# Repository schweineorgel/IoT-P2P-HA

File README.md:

Demostraciones reales del sistema disponibles en video (ver sección “Demostraciones en video”).

# Sistema IoT descentralizado con ESP32 y ESP-NOW

Sistema de automatización doméstica diseñado para operar de forma autónoma,
segura y tolerante a fallos, utilizando comunicación peer-to-peer entre nodos
ESP32 mediante ESP-NOW, sin dependencia de red Wi-Fi ni broker central.

## Alcance del repositorio y estructura de diseño

Este repositorio documenta el proceso completo de diseño, prototipado, validación experimental e iteración de un sistema IoT descentralizado con ESP32 y ESP-NOW.

Los módulos incluidos pueden encontrarse en distintos estados de abstracción:
- Versiones finales con esquemáticos y diseños PCB.
- Placas de interconexión (solo PCB) orientadas a exponer pines físicos.
- Versiones preliminares o simplificadas utilizadas durante el proceso de
  validación experimental.

Cada módulo se documenta en su propio directorio dentro de `hardware/`,
incluyendo:
- El propósito funcional.
- Nivel de abstracción (esquemático completo, solo PCB, placa de interconexión).
- Relación entre diseño y la implementación física real.
- Decisiones de diseño relevantes y limitaciones conocidas.

La estructura general del directorio `hardware/` es la siguiente:

```
hardware/
├── nodemcu_sensor_pcb
├── nodemcu_ssr_pcb
├── sensor_pcb
└── ssr_pcb
```
Cada uno de estos directorios incluye su propio README detallado.

## Cómo leer este repositorio

Este repositorio no está orientado a la reproducción directa del sistema,
sino a la comprensión del proceso de diseño y validación.

Se recomienda el siguiente orden de lectura:

1. README principal (este archivo), para entender la arquitectura general.
2. Directorio `hardware/`, donde cada módulo cuenta con un README específico.
3. Directorios de firmware y configuración (ESPHome / Home Assistant), según interés.

Cada módulo de hardware debe interpretarse como una unidad independiente,
con su propio contexto, alcance y nivel de madurez.

## Arquitectura general

El sistema está compuesto por nodos ESP32 que toman decisiones localmente y
se comunican entre sí mediante ESP-NOW. La supervisión mediante Home Assistant
es opcional y no afecta la operación del sistema ante caídas de red o servidor.

## Flujo de funcionamiento

1. El nodo sensor detecta presencia mediante radar mmWave.
2. Se evalúa la luminosidad ambiente.
3. Si se cumplen las condiciones, se envía un token de acción vía ESP-NOW.
4. El nodo actuador conmuta la carga y confirma la acción localmente.

## Notas de diseño e iteraciones

Durante el desarrollo del nodo actuador se realizaron varias iteraciones en el
diseño del SSR, motivadas por pruebas prácticas y validación experimental del
comportamiento del circuito.

> En la imagen se observan dos PCBs del SSR diseñado en KiCad: una vista frontal
> y una vista posterior.

En la cara posterior se aprecia la etapa de control basada en un transistor,
cuya resistencia en la base permite regular la amplificación de corriente en el
colector, junto a un LED indicador conectado en paralelo para señalización de
activación.
El emisor del transistor se conecta a tierra mediante un bypass implementado
con una resistencia de 0 Ω.

Esta configuración permite limitar la corriente suministrada al optoacoplador
(MOC), evitando la sobrecarga de los pines GPIO del ESP32 y manteniendo corrientes
de activación seguras, cercanas a los 9 mA por cada SSR activo.

### Desarrollo del SSR

El diseño inicial del SSR se basó en ingeniería inversa de un módulo comercial
capaz de operar con tensiones de control en un rango amplio (aprox. 3 V a 32 V).
Si bien el principio de funcionamiento era correcto, la reproducción directa
del diseño no resultó funcional al implementarse en una PCB propia, presentando
fallas de activación consistentes durante las pruebas.

Ante este comportamiento, se optó por una solución experimental que permitiera
controlar de forma más precisa la corriente de excitación del optoacoplador (MOC).
Para ello, se utilizó el LED indicador, que opera con corrientes del orden de
microamperes, junto con un transistor conectado en paralelo, actuando como una
etapa de control de corriente hacia el MOC, equivalente a una resistencia
variable, aprovechando las características de ganancia (hFE) del transistor.

Esta solución fue implementada y validada en tres SSR independientes, obteniendo
corrientes de activación muy similares entre unidades, lo que permitió confirmar
la reproducibilidad y estabilidad del enfoque.

Una vez validado el comportamiento del SSR en condiciones reales de carga, el
diseño fue posteriormente simplificado en la versión final, eliminando la etapa
activa cuando fue posible y ajustando la limitación de corriente mediante
resistencias, manteniendo un consumo seguro para los GPIO del ESP32.

### Elección del protocolo de comunicación

Inicialmente se evaluó el uso de MQTT como protocolo de comunicación entre nodos.
Sin embargo, debido a la latencia introducida por el broker y a la dependencia
de red, se optó por migrar a ESP-NOW.

El uso de comunicación peer-to-peer permitió reducir la latencia, eliminar
dependencias externas y garantizar la operación local del sistema ante caídas
de red o del servidor de supervisión.

## Fabricación de prototipos

Los prototipos de las placas PCB fueron diseñados en KiCad y posteriormente
fabricados mediante fresado CNC a partir de G-code generado con FlatCAM.

Este enfoque permitió iterar sobre el diseño del SSR, validar
cambios eléctricos en hardware real y ajustar parámetros de corriente y
activación sin depender de servicios externos de fabricación.

## Hardware – Implementación real

### Implementación de los nodos

El sistema está compuesto por dos ESP32 independientes que se comunican entre sí mediante ESP-NOW.
Uno de ellos actúa como nodo sensor, equipado con radar mmWave para detección de presencia y un sensor de luminosidad.
El segundo funciona como nodo actuador e integra un SSR diseñado en KiCad para el control seguro de carga eléctrica.

## Demostraciones en video

A continuación se incluyen videos demostrativos del funcionamiento real del
sistema en condiciones de uso, con el hardware y firmware descritos en este
repositorio.

### Control manual (override)

En este video se muestra el funcionamiento del nodo actuador cuando el sistema
se encuentra en modo *override*, permitiendo la conmutación manual de los SSR
desde Home Assistant.

El control manual no interfiere con la lógica distribuida del sistema y puede
habilitarse o deshabilitarse sin afectar la comunicación ESP-NOW entre nodos.

### Detección de presencia y activación automática

Este video muestra la detección de presencia mediante radar mmWave en el nodo
sensor y la posterior activación automática del nodo actuador bajo condiciones
de baja luminosidad.

La decisión se toma de forma local en el nodo sensor y se comunica al nodo
actuador mediante ESP-NOW, sin dependencia de red Wi-Fi ni servidor central.

### Home Assistant

> Las capturas de pantalla corresponden al servidor de Home Assistant
> ejecutándose en Docker sobre un MacBook Air A1465 utilizado como host de pruebas.

Home Assistant se utiliza como capa de supervisión y control manual (override),
sin actuar como punto único de fallo del sistema.

En el dashboard, el nodo **esp32-a** corresponde al nodo sensor, donde se
visualiza el estado de presencia detectada y el nivel de luminosidad ambiental
medido en lux.

El nodo **esp32-b** corresponde al nodo actuador. Desde este se permite el
control manual de hasta cuatro SSR independientes cuando el modo *override*
está habilitado. En modo automático, los SSR se activan de forma simultánea
cuando el nodo sensor (**esp32-a**) envía un token de activación al detectar
presencia bajo condiciones de baja luminosidad.

Los SSR permanecen activos mientras se mantenga la detección de presencia en
la habitación, desactivándose automáticamente al cesar dicha condición.

### ESPHome

ESPHome se emplea para la configuración y el monitoreo de los nodos ESP32.

## Estado del proyecto

El sistema se encuentra en un estado funcional y estable a nivel experimental.
No se contemplan nuevas funcionalidades mayores en el corto plazo, aunque
podrían realizarse mejoras menores o ajustes documentales.

El repositorio tiene como objetivo principal servir como referencia técnica
del proceso de diseño, prototipado e iteración de un sistema IoT descentralizado.

## Colaboración

El diseño del hardware, el desarrollo del firmware y la documentación del
sistema fueron realizados por el autor de este repositorio.

El ensamblaje y la soldadura de los prototipos fueron realizados con el apoyo
de un colaborador durante la etapa de prototipado.

## Tecnologías aplicadas
ESP32 | ESPHome | ESP-NOW | Home Assistant | Docker | Debian 12 | KiCad | YAML

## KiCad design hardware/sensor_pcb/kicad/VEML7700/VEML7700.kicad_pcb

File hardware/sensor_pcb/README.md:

## Diseño PCB

Esta placa corresponde a una placa de sensores dedicada, no a un nodo
independiente. Su función es alojar, alimentar y exponer las señales de los
sensores hacia una placa principal basada en ESP32 (NodeMCU).

El diseño integra un radar de presencia mmWave C4001 y un sensor de luminosidad
VEML7700, sin lógica de procesamiento propia. Ambos dispositivos son
alimentados directamente desde el pin de 3,3 V del ESP32, al cual esta
placa se conecta mediante un conector dedicado.

La placa actúa como interfaz eléctrica y mecánica entre los sensores y el
ESP32, dejando disponibles las siguientes señales:
- RX / TX para la comunicación con el radar mmWave.
- I²C (SDA / SCL) para el sensor de luminosidad.
- Alimentación y referencia a tierra comunes.

Este enfoque modular permite:
- Separar físicamente los sensores del microcontrolador.
- Facilitar pruebas, reemplazo de sensores y futuras iteraciones.
- Mantener el PCB del ESP32 libre de componentes específicos de sensado.

El PCB fue diseñado en KiCad y pensado para prototipado rápido mediante
fresado CNC.

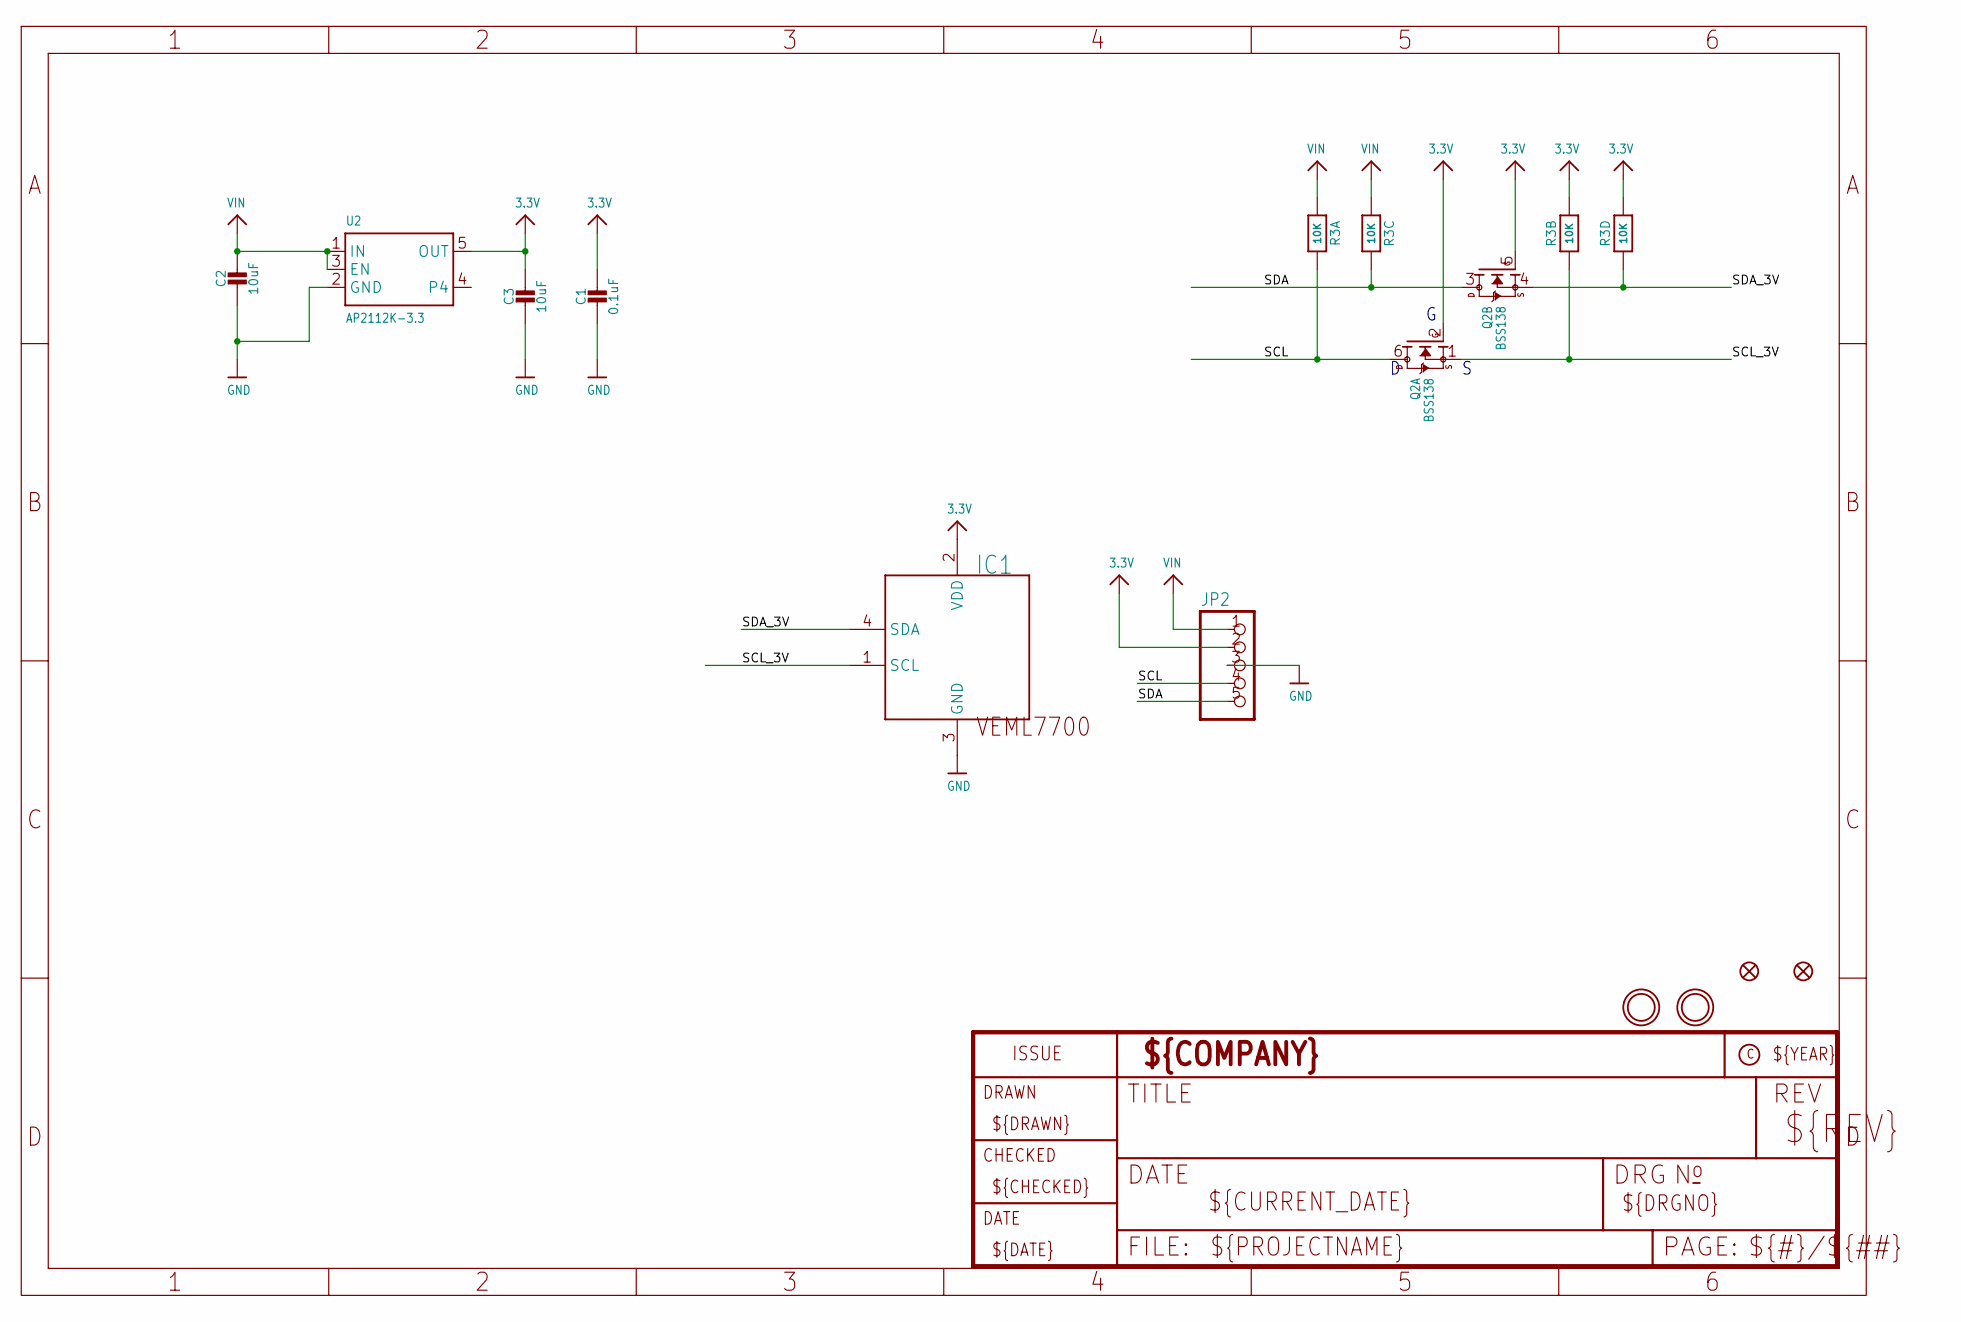
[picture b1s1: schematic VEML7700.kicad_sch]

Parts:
C1: 0.1uF; 0603-NO
C2, C3: 10uF; 0805-NO
FID1, FID2: FIDUCIAL_1MM
IC1: VEML7700
JP2: HEADER-1X5ROUND; 1X05_ROUND
Q2: BSS138; SOT363
R3: 10K; RESPACK_4X0603
U2: AP2112K-3.3; SOT23-5
U$3, U$4: MOUNTINGHOLE2.5; MOUNTINGHOLE_2.5_PLATED

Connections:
3.3V: C1.1, C3.1, IC1.2 (VDD), JP2.2, Q2.2 (G), Q2.5 (G), R3.2 (1), R3.4 (1), U2.5 (OUT)
GND: C1.2, C2.2, C3.2, IC1.3 (GND), JP2.3, U2.2 (GND)
SCL: JP2.4, Q2.6 (D), R3.8 (2)
SCL_3V: IC1.1 (SCL), Q2.1 (S), R3.7 (2)
SDA: JP2.5, Q2.3 (D), R3.6 (2)
SDA_3V: IC1.4 (SDA), Q2.4 (S), R3.5 (2)
VIN: C2.1, JP2.1, R3.1, R3.3 (1), U2.1 (IN), U2.3 (EN)

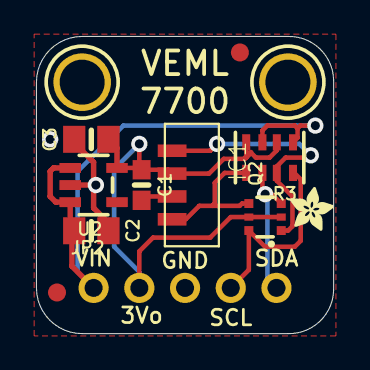
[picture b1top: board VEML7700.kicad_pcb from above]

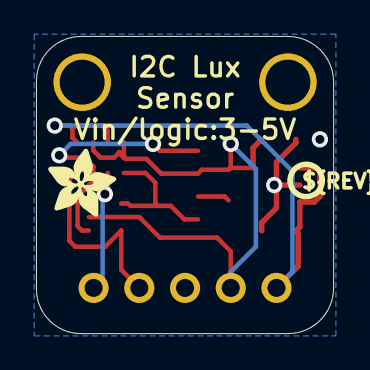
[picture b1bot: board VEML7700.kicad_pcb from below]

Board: 2 copper layers, 16.5 x 16.5 mm, 16 parts (3 on the bottom side), 7 nets.

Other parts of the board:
U$1: ADAFRUIT_3.5MM
U$8: ADAFRUIT_2.5MM
U$12: KATTNI_STOP
U$27: PCBFEAT-REV-040

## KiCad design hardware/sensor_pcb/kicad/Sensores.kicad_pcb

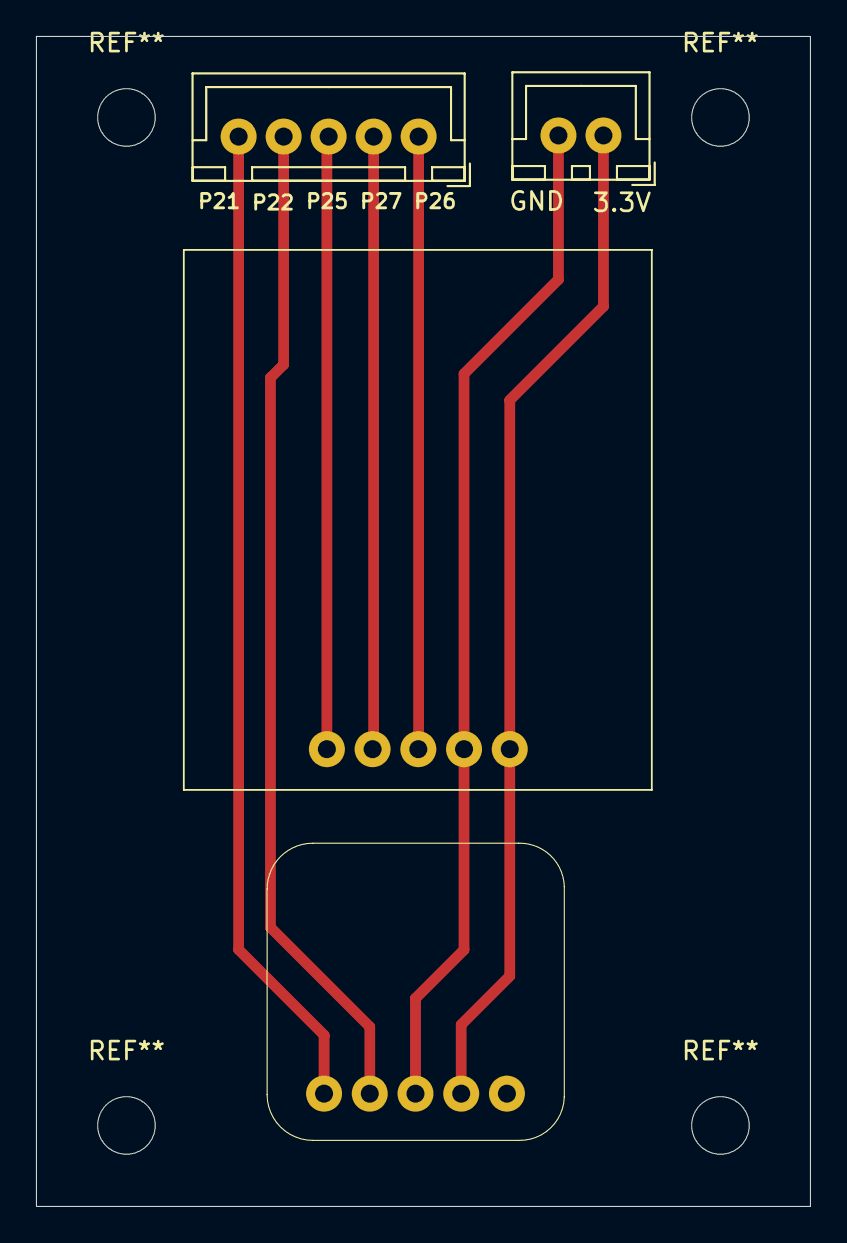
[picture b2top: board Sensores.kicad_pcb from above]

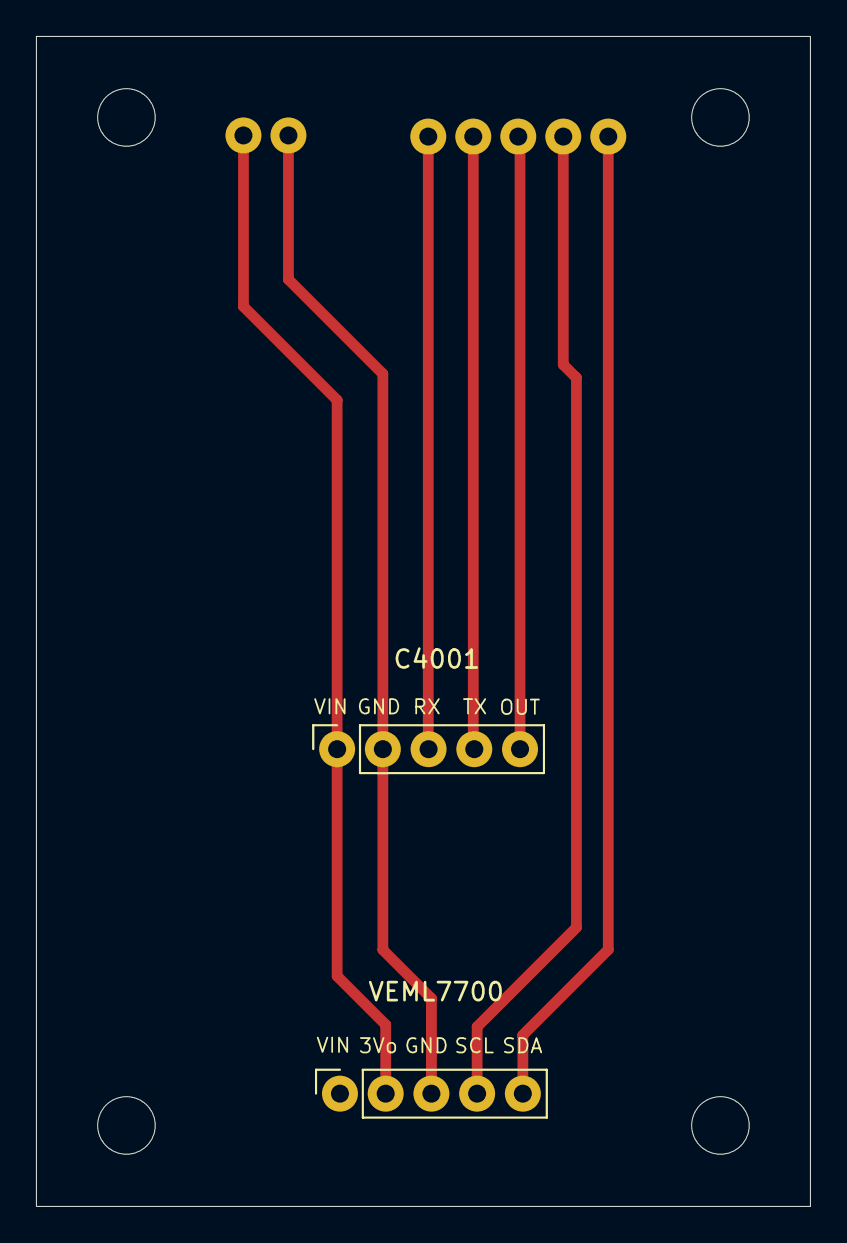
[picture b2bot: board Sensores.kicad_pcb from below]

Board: 2 copper layers, 43.0 x 65.0 mm, 4 parts (2 on the bottom side), 7 nets.

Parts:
3.3V: Conn_01x02_Socket; JST_XH_B2B-XH-A_1x02_P2.50mm_Vertical
C4001: Conn_01x05_Socket; PinSocket_1x05_P2.54mm_Vertical
J2: Conn_01x05_Socket; JST_XH_B5B-XH-A_1x05_P2.50mm_Vertical
VEML7700: Conn_01x05_Socket; PinSocket_1x05_P2.54mm_Vertical

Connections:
/3Vo: 3.3V.1, C4001.1, VEML7700.2
/OUT: C4001.5, J2.3
/RX: C4001.3, J2.1
/SCL: J2.4, VEML7700.4
/SDA: J2.5, VEML7700.5
/TX: C4001.4, J2.2
GND: 3.3V.2, C4001.2, VEML7700.3

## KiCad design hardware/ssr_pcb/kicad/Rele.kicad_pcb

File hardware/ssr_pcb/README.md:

## Diseño PCB

> **Nota sobre el esquemático final**  
> El esquemático y la vista PCB del SSR incluidos en este repositorio
> corresponden a una versión posterior del diseño y no coinciden
> exactamente con la implementación física utilizada en los prototipos
> funcionales.
>
> La PCB mostrada en el README principal corresponde a una versión
> preliminar validada experimentalmente, que incorpora una etapa de
> control basada en un transistor para limitar la corriente de excitación
> del optoacoplador (MOC).
>
> La versión documentada en este directorio refleja una iteración
> simplificada del diseño, donde la limitación de corriente se realiza
> exclusivamente mediante una resistencia en serie, manteniendo un LED
> indicador conectado en paralelo.

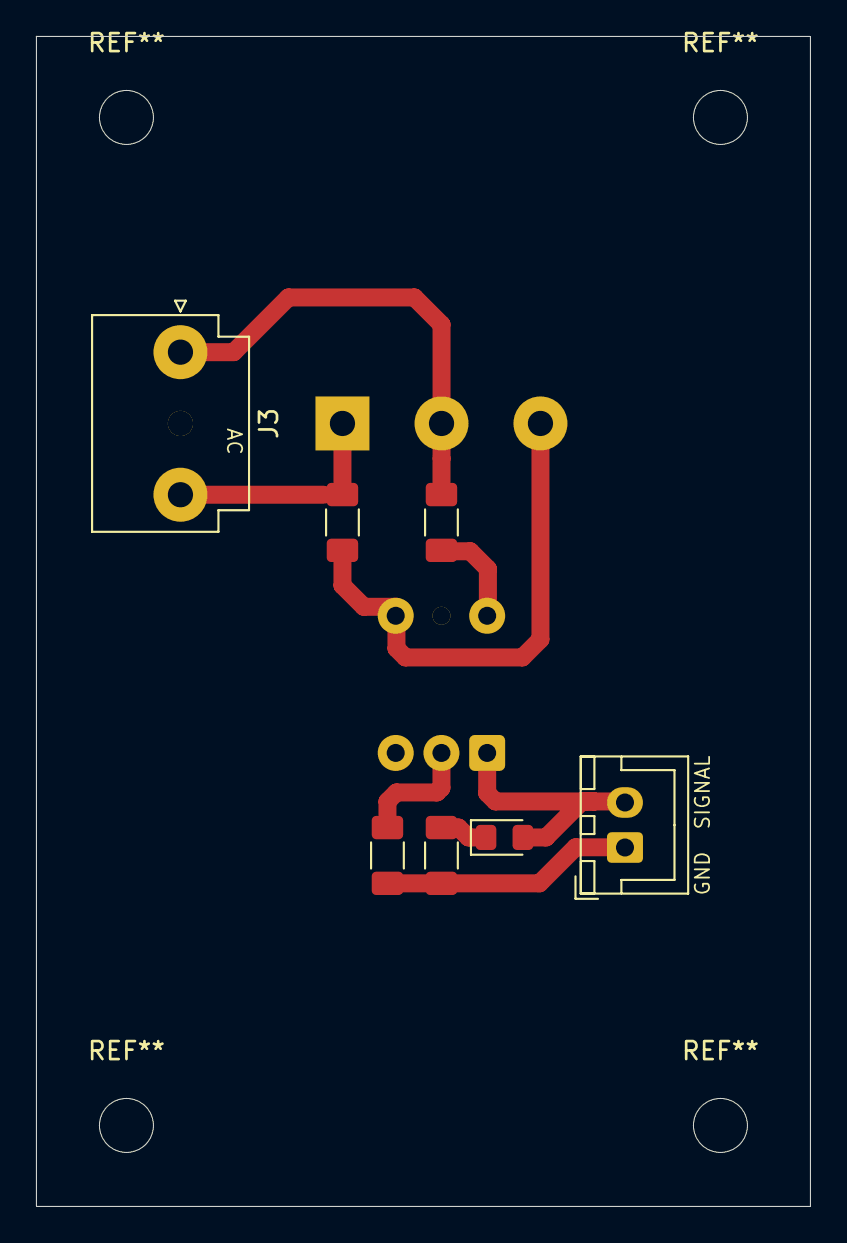
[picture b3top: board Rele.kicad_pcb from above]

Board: 2 copper layers, 43.0 x 65.0 mm, 8 parts (1 on the bottom side), 8 nets.

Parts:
D2: LED; LED_0805_2012Metric_Pad1.15x1.40mm_HandSolder
J2: Conn_01x02_Socket; JST_XH_B2B-XH-A_1x02_P2.50mm_Vertical
J3: Conn_01x03_Socket; JST_VH_B3P-VH_1x03_P3.96mm_Vertical
R1: 100; R_1206_3216Metric_Pad1.30x1.75mm_HandSolder
R2, R3: 330; R_1206_3216Metric_Pad1.30x1.75mm_HandSolder
R5: 10k; R_1206_3216Metric_Pad1.30x1.75mm_HandSolder
U1: MOC3063M; DIP-6_W7.62mm

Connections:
/HOT: J3.1, R1.2
/NEUTRAL: J3.3, R2.2
GND: J2.1, R3.1, R5.2
unnamed: D2.2 (A), J2.2, U1.1
unnamed: D2.1 (K), R5.1
unnamed: R2.1, U1.4
unnamed: R1.1, U1.6
unnamed: R3.2, U1.2

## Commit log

2026-01-03 added reference images for the sensor and actuator nodes. Updated README
2026-01-03 Update assets and README
2026-01-03 update schematic view for ssr and add screenshots with a README explaining design
2026-01-03 Update README.md for ssr
2026-01-03 added pcb and schematic screenshots to add to README for the design
2026-01-03 added README and screenshots for the actuator node's PCB
2026-01-03 Added README and screenshots for sensor node's PCB design
2026-01-03 added demonstrative videos
2026-01-03 added presence detector proof-of-concept video

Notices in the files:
README.md:
License: MIT
